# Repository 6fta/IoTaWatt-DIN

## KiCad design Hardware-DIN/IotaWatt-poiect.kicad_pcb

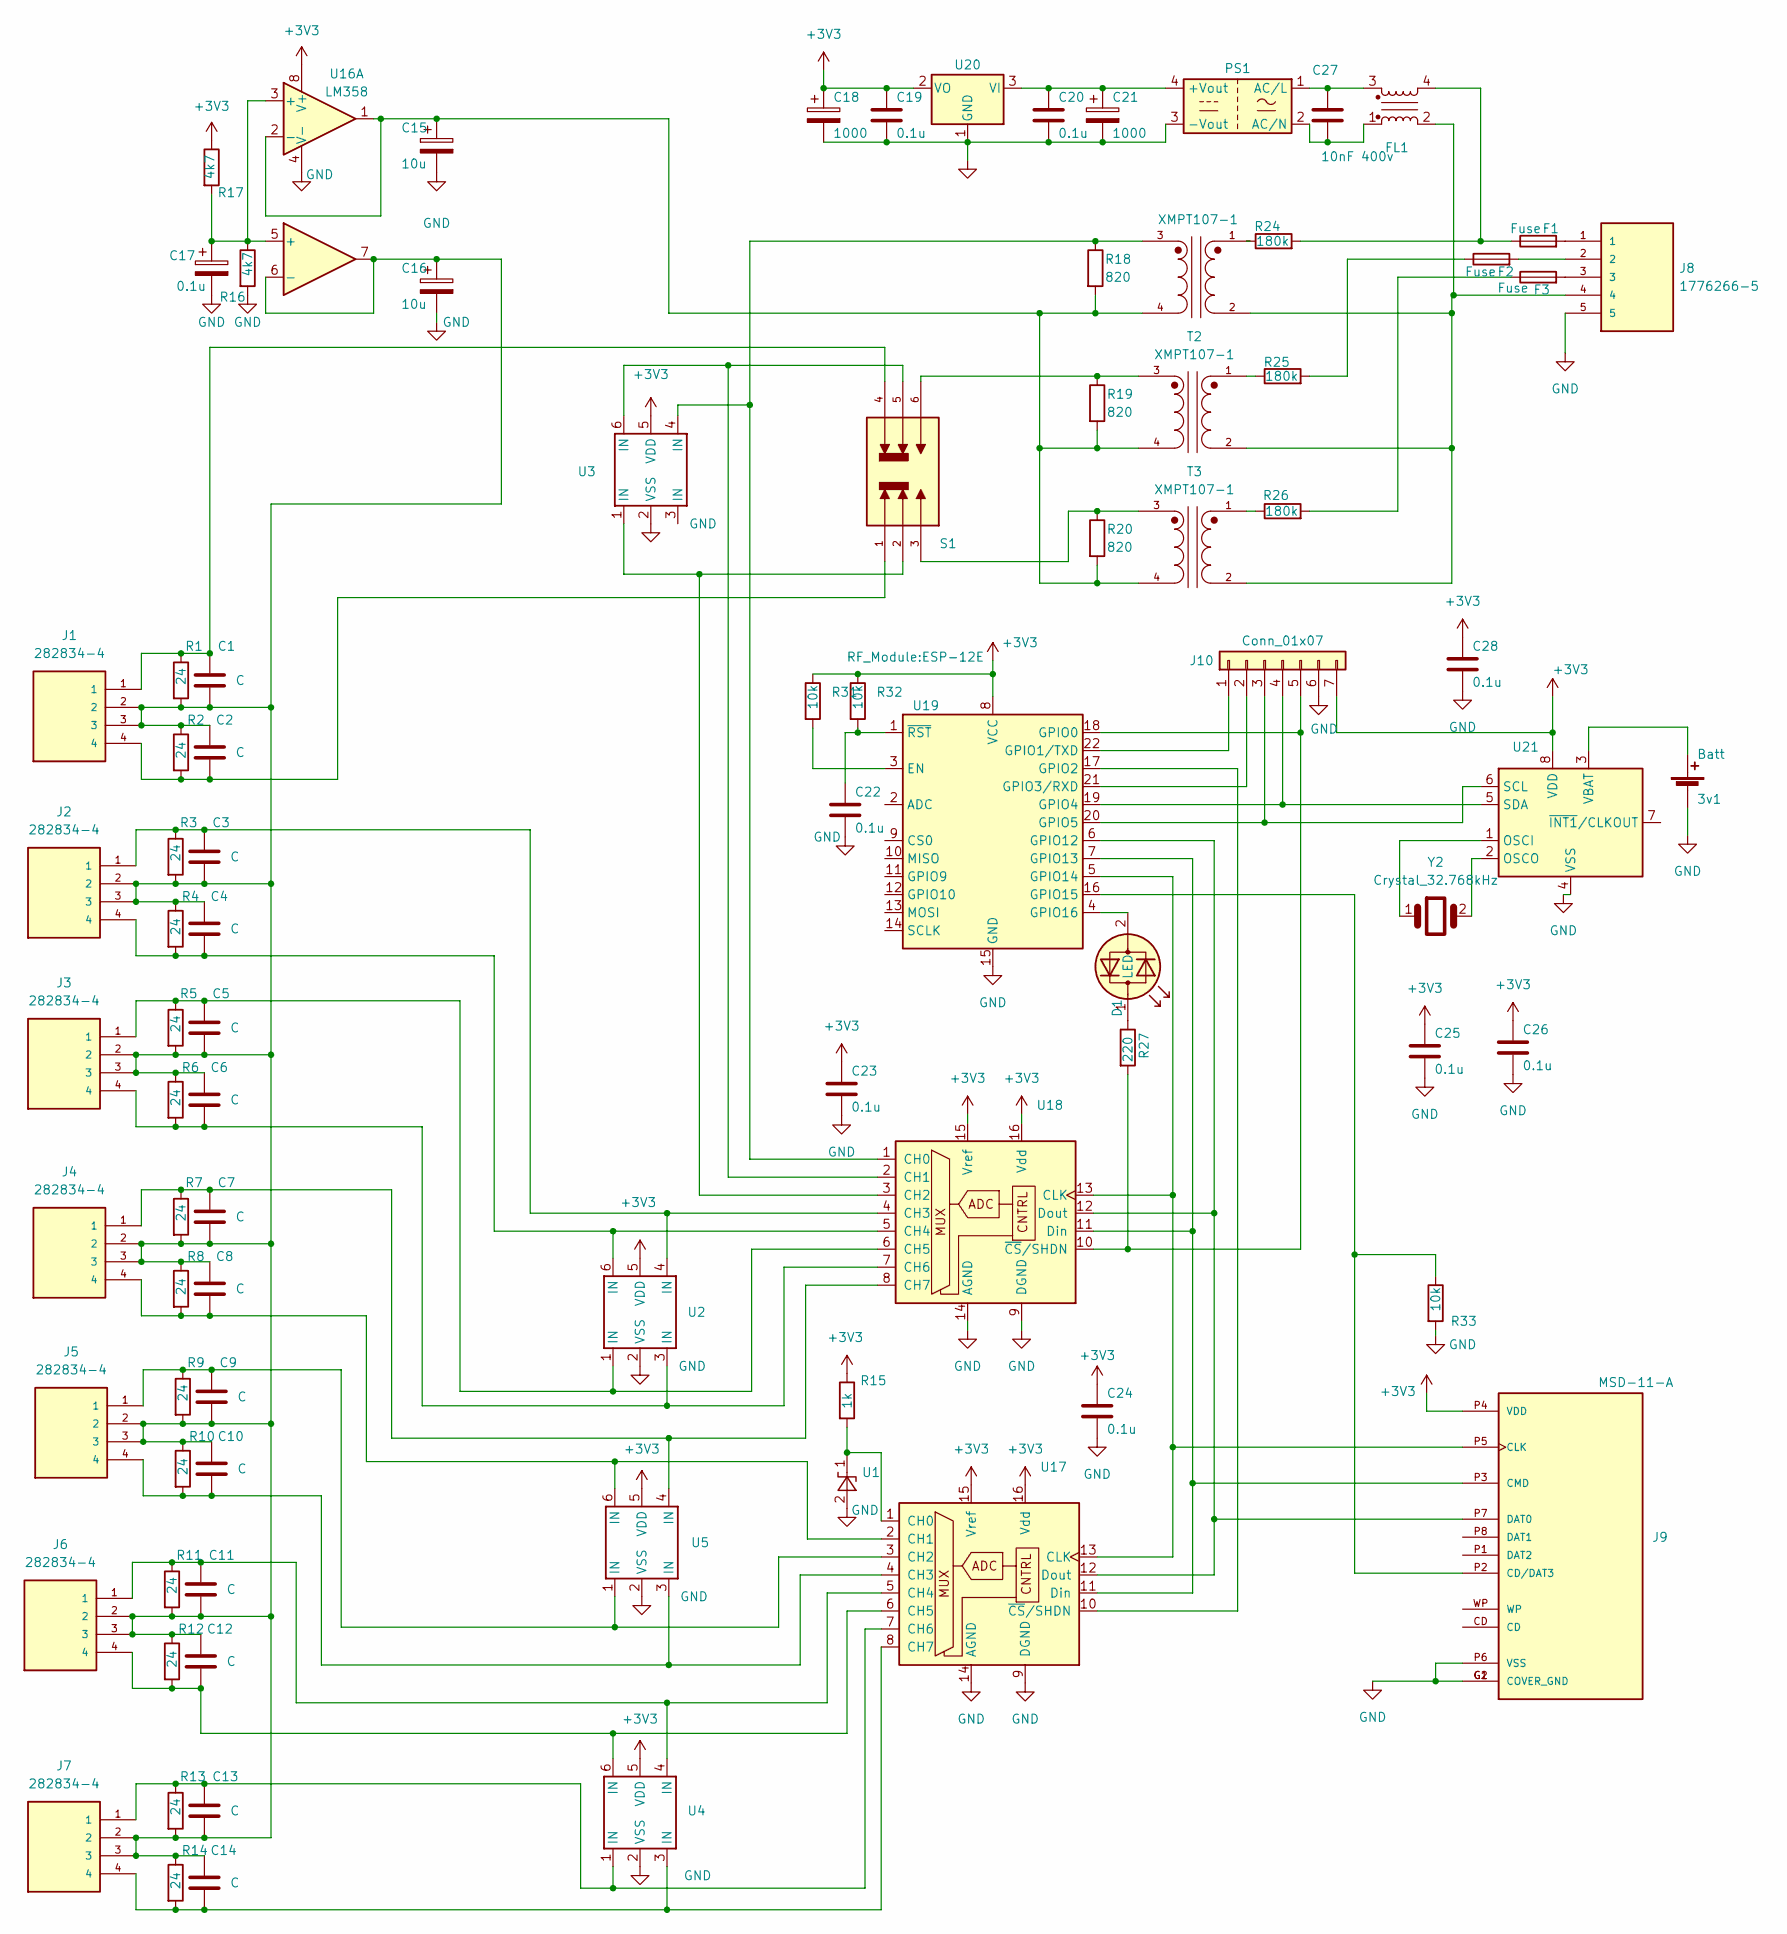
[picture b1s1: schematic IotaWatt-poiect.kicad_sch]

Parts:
3v1: Batt; BatteryHolder_LINX_BAT-HLD-012-SMT
C1, C2, C3, C4, C5, C6, C7, C8, C9, C10, C11, C12, C13, C14: C; C_0805_2012Metric
C15, C16: 10u; C_1206_3216Metric
C17: 0.1u; C_1206_3216Metric
C18, C21: 1000; CP_Radial_D10.0mm_P5.00mm
C19, C20, C22, C23, C24, C25, C26, C28: 0.1u; C_0805_2012Metric
C27: 10nF 400v; C_Rect_L16.5mm_W4.7mm_P15.00mm_MKT
D1: LED; LED_D3.0mm
F1, F2, F3: Fuse; FUSRR508W60L835T400H810
FL1: Choke_Schaffner_RN102-0.3-02-12M; UU9_choke
J1, J2, J3, J4, J5, J6, J7: 282834-4; TE_282834-4
J8: 1776266-5; TE_1776266-5
J9: MSD-11-A; CUI_MSD-11-A; PARTREV 1.02
J10: Conn_01x07; PinSocket_1x07_P2.54mm_Vertical
PS1: HLK-PM01; Converter_ACDC_HiLink_HLK-PMxx
R1, R2, R3, R4, R5, R6, R7, R8, R9, R10, R11, R12, R13, R14: 24; R_0805_2012Metric
R15: 1k; R_0805_2012Metric
R16, R17: 4k7; R_0805_2012Metric
R18, R19, R20: 820; R_0805_2012Metric
R24, R25, R26: 180k; R_Axial_DIN0207_L6.3mm_D2.5mm_P2.54mm_Vertical
R27: 220; R_0805_2012Metric
R31, R32, R33: 10k; R_0805_2012Metric
S1: JS202011SCQN; SW_JS202011SCQN; PARTREV 26 May 22
T1, T2, T3: XMPT107-1; ZMPT107-1
U1: LM4040D25FTA; SOT-23
U2, U3, U4, U5: D5V0P4UR6SO-7
U16: LM358; SOIC-8_3.9x4.9mm_P1.27mm
U17, U18: MCP3208; SOP-16_3.9x9.9mm_P1.27mm
U19: ESP-12F; ESP-12E
U20: AMS1117-3.3; SOT-223-3_TabPin2
U21: PCF8523T; SOIC-8_3.9x4.9mm_P1.27mm
Y2: Crystal_32.768kHz; Crystal_AT310_D3.0mm_L10.0mm_Horizontal

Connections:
+3V3: C18.1, C19.1, C23.1, C24.1, C25.1, C26.1, C28.1, J9.P4 (VDD), J10.7, R15.1, R17.1, R31.1, R32.1, U2.5 (VDD), U3.5 (VDD), U4.5 (VDD), U5.5 (VDD), U16.8 (V+), U17.15 (Vref), U17.16 (Vdd), U18.15 (Vref), U18.16 (Vdd), U19.8 (VCC), U20.2 (VO), U21.8 (VDD)
GND: 3v1.2 (-), C15.2, C16.2, C17.2, C18.2, C19.2, C20.2, C21.2, C22.2, C23.2, C24.2, C25.2, C26.2, C28.2, J8.5, J9.G1 (COVER_GND), J9.G2 (COVER_GND), J9.P6 (VSS), J10.6, PS1.3 (-Vout), R16.2, R33.2, U1.2 (A), U2.2 (VSS), U3.2 (VSS), U4.2 (VSS), U5.2 (VSS), U16.4 (V-), U17.9 (DGND), U17.14 (AGND), U18.9 (DGND), U18.14 (AGND), U19.15 (GND), U20.1 (GND), U21.4 (VSS)
unnamed: 3v1.1 (+), U21.3 (VBAT)
unnamed: C1.1, J1.1, R1.1, S1.4
unnamed: C2.2, J1.4, R2.2, S1.1
unnamed: D1.2 (AK), U19.4 (GPIO16)
unnamed: D1.1 (KA), R27.1
unnamed: F1.1, FL1.4, R24.2
unnamed: F1.2, J8.1
unnamed: F2.1, R25.2
unnamed: F2.2, J8.2
unnamed: F3.1, R26.2
unnamed: F3.2, J8.3
unnamed: FL1.2, J8.4, T1.2, T2.2, T3.2
unnamed: J9.P2 (CD/DAT3), R33.1, U19.16 (GPIO15)
unnamed: J9.P5 (CLK), U17.13 (CLK), U18.13 (CLK), U19.5 (GPIO14)
unnamed: J9.P3 (CMD), U17.11 (Din), U18.11 (Din), U19.7 (GPIO13)
unnamed: J9.P7 (DAT0), U17.12 (Dout), U18.12 (Dout), U19.6 (GPIO12)
unnamed: J10.1, U19.22 (GPIO1/TXD)
unnamed: J10.2, U19.21 (GPIO3/RXD)
unnamed: J10.3, U19.20 (GPIO5), U21.6 (SCL)
unnamed: J10.4, U19.19 (GPIO4), U21.5 (SDA)
unnamed: J10.5, R27.2, U18.10 (~CS/SHDN), U19.18 (GPIO0)
unnamed: C20.1, C21.1, PS1.4 (+Vout), U20.3 (VI)
unnamed: C27.1, FL1.3, PS1.1 (AC/L)
unnamed: C27.2, FL1.1, PS1.2 (AC/N)
unnamed: R19.1, S1.6, T2.3
unnamed: R20.1, S1.3, T3.3
unnamed: R24.1, T1.1
unnamed: R25.1, T2.1
unnamed: R26.1, T3.1
unnamed: R15.2, U1.1 (K), U17.1 (CH0)
unnamed: C17.1, R16.1, R17.2, U16.3 (+), U16.5 (+)
unnamed: C15.1, R18.2, R19.2, R20.2, T1.4, T2.4, T3.4, U16.1, U16.2 (-)
unnamed: C1.2, C2.1, C3.2, C4.1, C5.2, C6.1, C7.2, C8.1, C9.2, C10.1, C11.2, C12.1, C13.2, C14.1, C16.1, J1.2, J1.3, J2.2, J2.3, J3.2, J3.3, J4.2, J4.3, J5.2, J5.3, J6.2, J6.3, J7.2, J7.3, R1.2, R2.1, R3.2, R4.1, R5.2, R6.1, R7.2, R8.1, R9.2, R10.1, R11.2, R12.1, R13.2, R14.1, U16.6 (-), U16.7
unnamed: C8.2, J4.4, R8.2, U5.6 (IN), U17.2 (CH1)
unnamed: C9.1, J5.1, R9.1, U5.1 (IN), U17.3 (CH2)
unnamed: C10.2, J5.4, R10.2, U5.3 (IN), U17.4 (CH3)
unnamed: C11.1, J6.1, R11.1, U4.4 (IN), U17.5 (CH4)
unnamed: C12.2, J6.4, R12.2, U4.6 (IN), U17.6 (CH5)
unnamed: C13.1, J7.1, R13.1, U4.1 (IN), U17.7 (CH6)
unnamed: C14.2, J7.4, R14.2, U4.3 (IN), U17.8 (CH7)
unnamed: U17.10 (~CS/SHDN), U19.17 (GPIO2)
unnamed: R18.1, T1.3, U3.4 (IN), U18.1 (CH0)
unnamed: S1.5, U3.6 (IN), U18.2 (CH1)
unnamed: S1.2, U3.1 (IN), U18.3 (CH2)
unnamed: C3.1, J2.1, R3.1, U2.4 (IN), U18.4 (CH3)
unnamed: C4.2, J2.4, R4.2, U2.6 (IN), U18.5 (CH4)
unnamed: C5.1, J3.1, R5.1, U2.1 (IN), U18.6 (CH5)
unnamed: C6.2, J3.4, R6.2, U2.3 (IN), U18.7 (CH6)
unnamed: C7.1, J4.1, R7.1, U5.4 (IN), U18.8 (CH7)
unnamed: R31.2, U19.3 (EN)
unnamed: C22.1, R32.2, U19.1 (~RST)
unnamed: U21.1 (OSCI), Y2.1
unnamed: U21.2 (OSCO), Y2.2

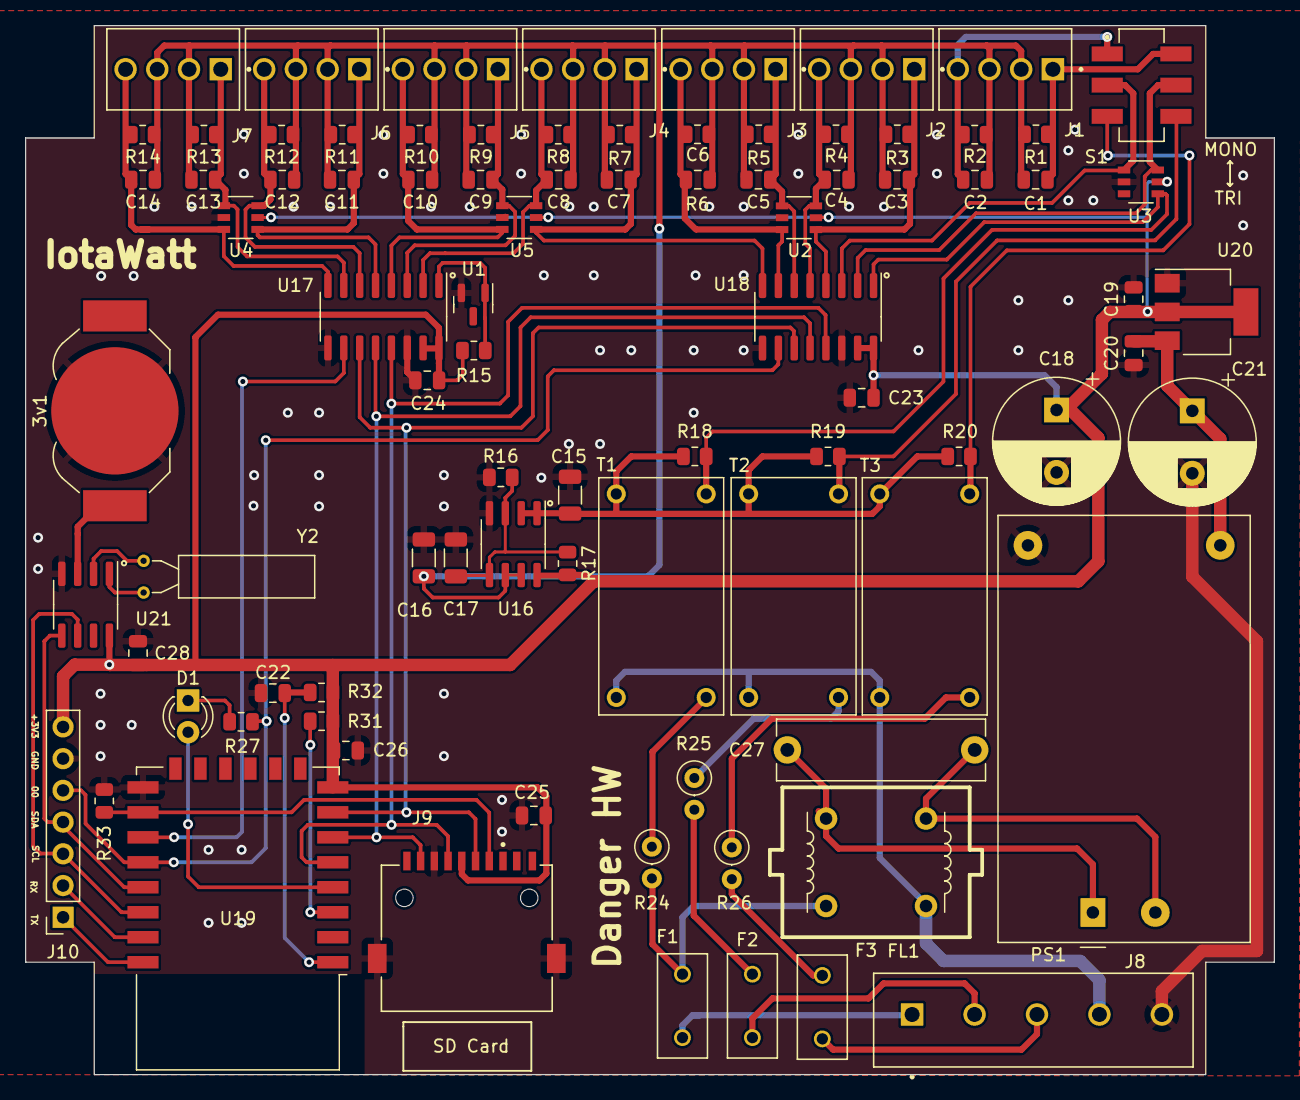
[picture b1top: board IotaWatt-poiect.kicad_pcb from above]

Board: 2 copper layers, 100.0 x 84.0 mm, 88 parts (0 on the bottom side), 55 nets.

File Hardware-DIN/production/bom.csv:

Designator,Footprint,Quantity,Value,LCSC Part #
3V1,BatteryHolder_LINX_BAT-HLD-012-SMT,1,Batt,
"C1, C10, C11, C12, C13, C14, C2, C3, C4, C5, C6, C7, C8, C9",0805,14,C,
"C15, C16",1206,2,10u,
C17,1206,1,0.1u,
"C18, C21",CP_Radial_D10.0mm_P5.00mm,2,1000,
"C19, C20, C22, C23, C24, C25, C26, C28",0805,8,0.1u,
C27,C_Rect_L16.5mm_W4.7mm_P15.00mm_MKT,1,10nF 400v,
D1,LED_D3.0mm,1,LED,
"F1, F2, F3",FUSRR508W60L835T400H810,3,Fuse,
FL1,UU9_choke,1,Choke_Schaffner_RN102-0.3-02-12M,
"J1, J2, J3, J4, J5, J6, J7",TE_282834-4,7,282834-4,
J10,PinSocket_1x07_P2.54mm_Vertical,1,Conn_01x07,
J8,TE_1776266-5,1,1776266-5,
J9,CUI_MSD-11-A,1,MSD-11-A,
PS1,Converter_ACDC_HiLink_HLK-PMxx,1,HLK-PM01,
"R1, R10, R11, R12, R13, R14, R2, R3, R4, R5, R6, R7, R8, R9",0805,14,24,
R15,0805,1,1k,
"R16, R17",0805,2,4k7,
"R18, R19, R20",0805,3,820,
"R24, R25, R26",R_Axial_DIN0207_L6.3mm_D2.5mm_P2.54mm_Vertical,3,180k,
R27,0805,1,220,
"R31, R32, R33",0805,3,10k,
S1,SW_JS202011SCQN,1,JS202011SCQN,
"T1, T2, T3",ZMPT107-1,3,XMPT107-1,
U1,SOT-23,1,LM4040D25FTA,
U16,SOIC-8_3.9x4.9mm_P1.27mm,1,LM358,
"U17, U18",SOP-16_3.9x9.9mm_P1.27mm,2,MCP3208,
U19,ESP-12E,1,ESP-12F,
"U2, U3, U4, U5",D5V0P4UR6SO-7,4,D5V0P4UR6SO-7,
U20,SOT-223-3_TabPin2,1,AMS1117-3.3,
U21,SOIC-8_3.9x4.9mm_P1.27mm,1,PCF8523T,
Y2,Crystal_AT310_D3.0mm_L10.0mm_Horizontal,1,Crystal_32.768kHz,

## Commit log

2025-04-05 IotaWattDIN
